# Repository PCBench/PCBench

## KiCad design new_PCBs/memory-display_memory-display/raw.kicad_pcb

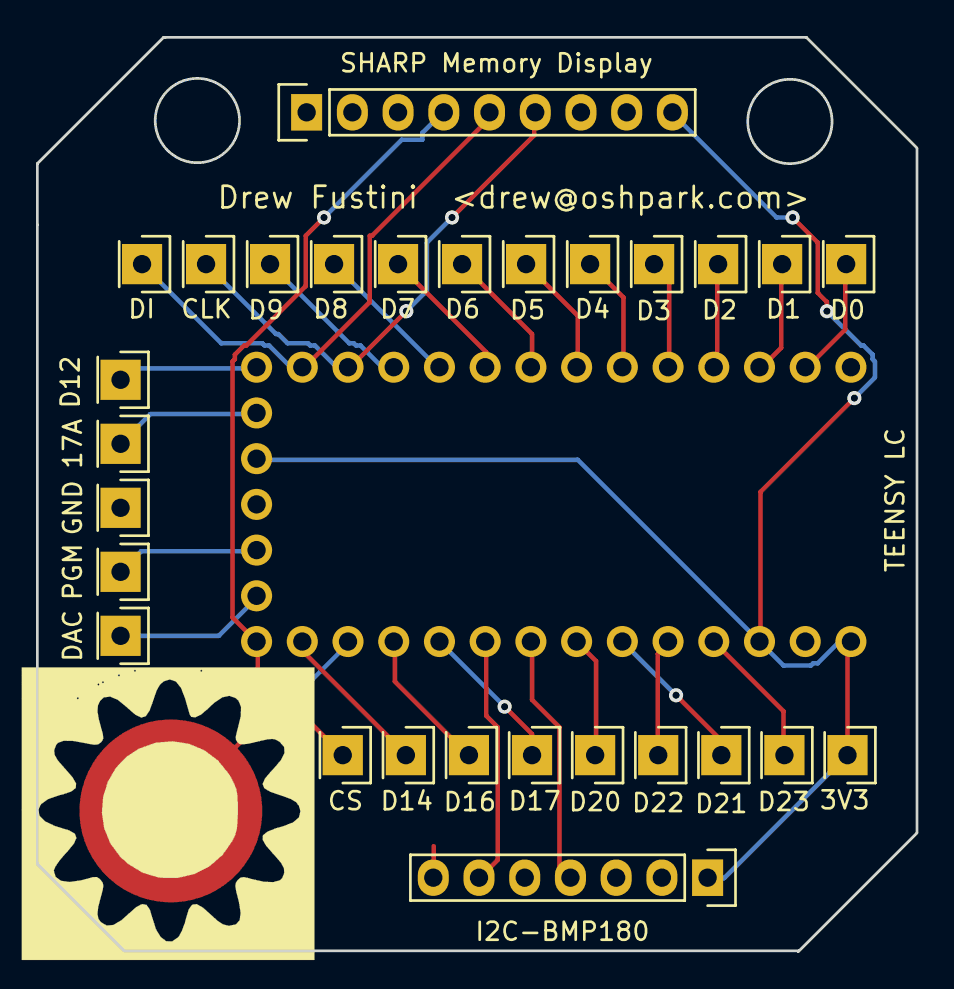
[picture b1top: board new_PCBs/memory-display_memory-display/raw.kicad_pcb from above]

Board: 2 copper layers, 48.9 x 50.8 mm, 30 parts (0 on the bottom side), 29 nets.

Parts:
3V3: 3v3; CONN-HEADER-STRAIGHT-P2.54MM-1x01
17A: 17A; CONN-HEADER-STRAIGHT-P2.54MM-1x01
CAP15: CAP15; CAPSENSE-CIRCLE-D10MM
CLK: CLK; CONN-HEADER-STRAIGHT-P2.54MM-1x01
CS: CS; CONN-HEADER-STRAIGHT-P2.54MM-1x01
D0: D0; CONN-HEADER-STRAIGHT-P2.54MM-1x01
D1: D1; CONN-HEADER-STRAIGHT-P2.54MM-1x01
D2: D2; CONN-HEADER-STRAIGHT-P2.54MM-1x01
D3: D3; CONN-HEADER-STRAIGHT-P2.54MM-1x01
D4: D4; CONN-HEADER-STRAIGHT-P2.54MM-1x01
D5: D5; CONN-HEADER-STRAIGHT-P2.54MM-1x01
D6: D6; CONN-HEADER-STRAIGHT-P2.54MM-1x01
D7: D7; CONN-HEADER-STRAIGHT-P2.54MM-1x01
D8: D8; CONN-HEADER-STRAIGHT-P2.54MM-1x01
D9: D9; CONN-HEADER-STRAIGHT-P2.54MM-1x01
D12: D12; CONN-HEADER-STRAIGHT-P2.54MM-1x01
D14: D14; CONN-HEADER-STRAIGHT-P2.54MM-1x01
D16: D16; CONN-HEADER-STRAIGHT-P2.54MM-1x01
D17: D17; CONN-HEADER-STRAIGHT-P2.54MM-1x01
D20: D20; CONN-HEADER-STRAIGHT-P2.54MM-1x01
D21: D21; CONN-HEADER-STRAIGHT-P2.54MM-1x01
D22: D22; CONN-HEADER-STRAIGHT-P2.54MM-1x01
D23: D23; CONN-HEADER-STRAIGHT-P2.54MM-1x01
DAC: DAC; CONN-HEADER-STRAIGHT-P2.54MM-1x01
DI: DI; CONN-HEADER-STRAIGHT-P2.54MM-1x01
GND: PGM; CONN-HEADER-STRAIGHT-P2.54MM-1x01
I2C-BMP180: I2C-BMP180; Pin_Header_Straight_1x07
J1: TEENSY-LC
PGM: PGM; CONN-HEADER-STRAIGHT-P2.54MM-1x01
SHARP Memory Display: SHARP-MEM-DISP; Pin_Header_Straight_1x09

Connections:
+3V3: 3V3.1, I2C-BMP180.1, J1.3V1, J1.3V2, J1.VIN, SHARP Memory Display.9
/CLK: CLK.1, J1.10, SHARP Memory Display.6
/CS: CS.1, I2C-BMP180.7, J1.13, SHARP Memory Display.4
/D0: D0.1, J1.0
/D1: D1.1, J1.1
/D2: D2.1, J1.2
/D3: D3.1, J1.3
/D4: D4.1, J1.4
/D5: D5.1, J1.5
/D6: D6.1, J1.6
/D7: D7.1, J1.7
/D8: D8.1, J1.8
/D9: D9.1, J1.9
/D11: DI.1, J1.11, SHARP Memory Display.5
/D12: D12.1, J1.12
/D14: D14.1, J1.14
/D15: CAP15.1, J1.15
/D16: D16.1, J1.16
/D17: D17.1, J1.17
/D17(VIN): 17A.1, J1.17A
/D18: I2C-BMP180.6, J1.18
/D19: I2C-BMP180.4, J1.19
/D20: D20.1, J1.20
/D21: D21.1, J1.21
/D22: D22.1, J1.22
/D23: D23.1, J1.23
/DAC: DAC.1, J1.DAC
/PROG: J1.PGM, PGM.1
GND: GND.1, I2C-BMP180.3, J1.G1, J1.G2, J1.G3, SHARP Memory Display.7

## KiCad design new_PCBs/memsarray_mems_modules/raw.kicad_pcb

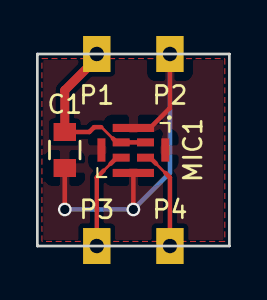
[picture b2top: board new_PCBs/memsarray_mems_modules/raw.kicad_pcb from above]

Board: 2 copper layers, 10.7 x 10.7 mm, 6 parts (0 on the bottom side), 4 nets.

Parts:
C1: 1uF; C_0805
MIC1: MEMS_MIC; Mic-MEMS_Top_8_pins
P1, P2, P3, P4: CASTELLATED_PAD; Castellated_Pad

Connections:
/CLK: MIC1.3, P3.1
/OUT: MIC1.4, P4.1
DGND: C1.2, MIC1.5, P2.1
DVDD: C1.1, MIC1.1, MIC1.2, P1.1

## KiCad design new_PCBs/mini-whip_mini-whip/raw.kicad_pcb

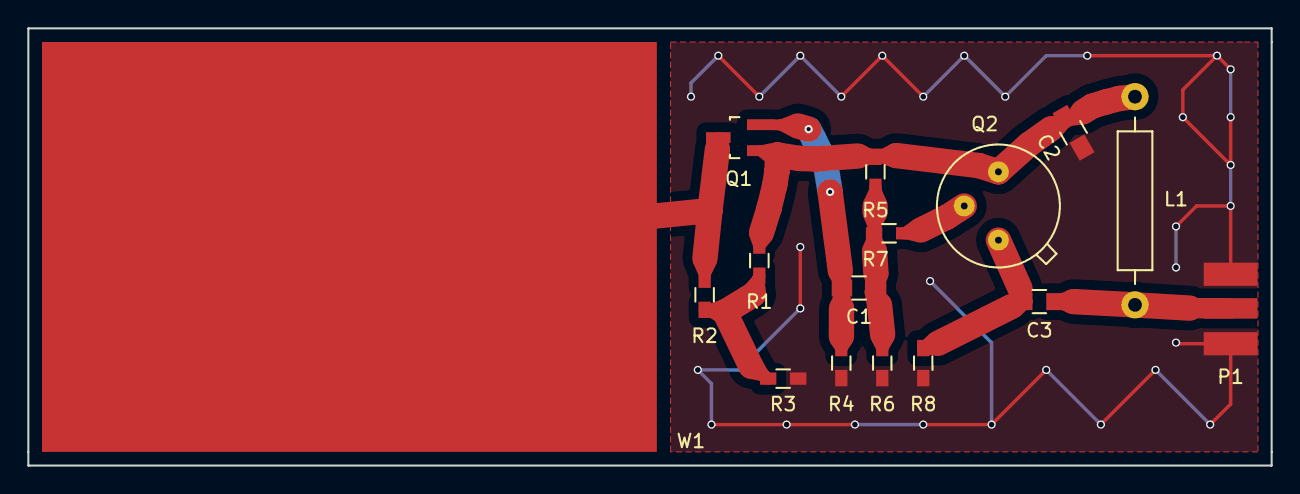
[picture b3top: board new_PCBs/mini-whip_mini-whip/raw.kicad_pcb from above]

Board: 2 copper layers, 91.0 x 32.0 mm, 17 parts (1 on the bottom side), 9 nets.

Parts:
C1, C2, C3: 560n; C_0805_HandSoldering
L1: 470 uH; Choke_Horizontal_RM15mm
P1, P1#2: SMA-J
Q1: MMBFJ310; SOT-23_Handsoldering
Q2: 2N5109; M246
R1, R2, R3: 1M; R_0603_HandSoldering
R4: 680; R_0603_HandSoldering
R5: 2k2; R_0603_HandSoldering
R6: 10k; R_0603_HandSoldering
R7: 47; R_0603_HandSoldering
R8: 220; R_0603_HandSoldering
W1: MINIWHIP

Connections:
Earth: C2.1, P1.2, P1#2.2, R3.2, R4.2, R6.2, R8.2
unnamed: C1.1, R5.2, R6.1, R7.2
unnamed: C1.2, Q1.2, R4.1
unnamed: C2.2, L1.1, Q1.1, Q2.3, R1.1, R5.1
unnamed: C3.1, L1.2, P1.1, P1#2.1
unnamed: C3.2, Q2.1, R8.1
unnamed: Q1.3, R2.1, W1.1
unnamed: Q2.2, R7.1
unnamed: R1.2, R2.2, R3.1

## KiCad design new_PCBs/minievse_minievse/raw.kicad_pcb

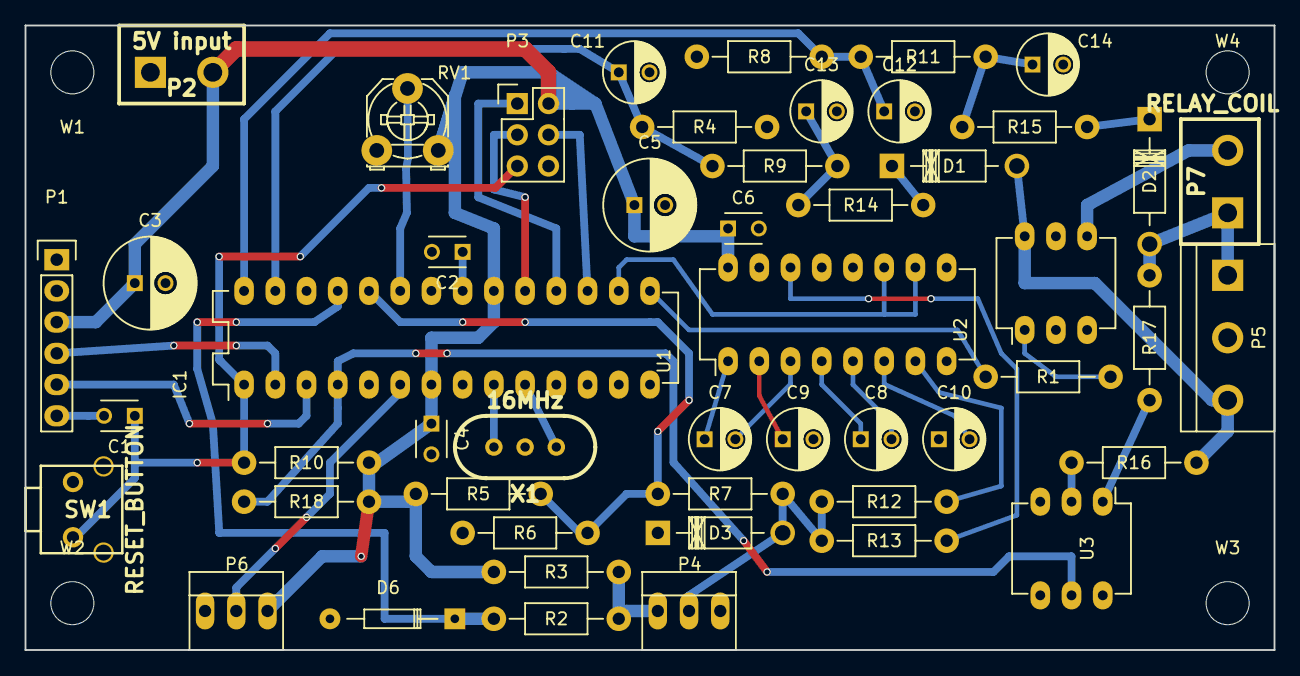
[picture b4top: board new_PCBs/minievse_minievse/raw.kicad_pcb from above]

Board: 2 copper layers, 101.6 x 50.8 mm, 54 parts (0 on the bottom side), 41 nets.

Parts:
C1, C2, C4, C6: 104; C_Disc_D3_P2.5
C3, C5: 100uF; C_Radial_D7.5_L11.2_P2.5
C7, C8, C9, C10: 1uF; C_Radial_D5_L6_P2.5
C11, C12, C13, C14: 10uF; C_Radial_D5_L6_P2.5
D1, D2: 1N4007; Diode_DO-41_SOD81_Horizontal_RM10_refdes_in_box
D3: P6KE16CA; Diode_DO-41_SOD81_Horizontal_RM10_refdes_in_box
D6: 1N4148; Diode_DO-35_SOD27_Horizontal_RM10
IC1: ATMEGA328P-P; DIP-28_W7.62mm_LongPads
P1: SERIAL; Pin_Header_Straight_1x06
P2: 5V input; CCFLHV
P3: ICSP; Pin_Header_Straight_2x03
P4: Pilot; PINHEAD1-3
P5: AC_GND_AC; bornier3
P6: LED_STRIP; PINHEAD1-3
P7: RELAY_COIL; CCFLHV
R1: 220; Resistor_Horizontal_RM10mm_refdes_in_box
R2, R10, R18: 10K; Resistor_Horizontal_RM10mm_refdes_in_box
R3: 1K; Resistor_Horizontal_RM10mm_refdes_in_box
R4, R8, R9, R11: 2550; Resistor_Horizontal_RM10mm_refdes_in_box
R5: 56K; Resistor_Horizontal_RM10mm_refdes_in_box
R6: 100K; Resistor_Horizontal_RM10mm_refdes_in_box
R7: 200K; Resistor_Horizontal_RM10mm_refdes_in_box
R12, R13: 1200; Resistor_Horizontal_RM10mm_refdes_in_box
R14, R15: 50K; Resistor_Horizontal_RM10mm_refdes_in_box
R16, R17: 15K; Resistor_Horizontal_RM10mm_refdes_in_box
RV1: POT; Potentiometer_Triwood_RM-065
SW1: RESET_BUTTON; SW-1825027-5
U1: MAX232; DIP-16_W7.62mm_LongPads
U2: MOC3021M; DIP-6_W7.62mm_LongPads
U3: H11AA; DIP-6_W7.62mm_LongPads
W1, W2, W3, W4: MountingHole_3.5mm
X1: 16MHz; HC-49V-OR-RESONATOR

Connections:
+5VD: C3.1, C4.1, C5.1, C6.1, IC1.7, IC1.20, P1.3, P2.2, P3.2, P6.3, R3.2, R5.1, R10.1, R18.1, RV1.3, U1.16
/AC_SENSE_1: C11.1, IC1.27, R4.1, R9.2
/AC_SENSE_2: C12.1, IC1.28, R8.1, R11.2
/AC_ZEROX: IC1.4, R18.2, U3.5
/AMP_KNOB: IC1.23, RV1.2
/LED_DATA: IC1.6, P6.2
/PILOT: D3.2, P4.2, R7.1, R12.1, R13.1
/PILOTREAD: IC1.24, R5.2, R6.1, R7.2
/PP: P4.1, R2.2, R3.1
/PP_READ: D6.1, IC1.25, R2.1
/PWM: IC1.16, U1.10, U1.11
/RELAY_TRIAC: IC1.15, R1.2
/RX: IC1.2, P1.4
/TX: IC1.3, P1.5
/miso: IC1.18, P3.1
/mosi: IC1.17, P3.4
/reset: C1.1, IC1.1, P3.5, R10.2, SW1.1
/sck: IC1.19, P3.3
GND: C2.2, C3.2, C4.2, C5.2, C6.2, C9.2, C10.1, C11.2, C12.2, C13.2, C14.2, D3.1, D6.2, IC1.8, IC1.22, P1.2, P2.1, P3.6, P4.3, P5.2, P6.1, R4.2, R6.2, R8.2, RV1.1, SW1.2, U1.15, U2.2, U3.4, X1.3
unnamed: C1.2, P1.6
unnamed: C2.1, IC1.21
unnamed: C7.1, U1.1
unnamed: C7.2, U1.3
unnamed: C8.1, U1.4
unnamed: C8.2, U1.5
unnamed: C9.1, U1.2
unnamed: C10.2, U1.6
unnamed: C13.1, R9.1, R14.1
unnamed: C14.1, R11.1, R15.1
unnamed: D2.2, P5.1, P7.1, R17.2
unnamed: D1.1, R14.2
unnamed: D1.2, P5.3, R16.2, U2.6
unnamed: D2.1, R15.2
unnamed: IC1.9, X1.2
unnamed: IC1.10, X1.1
unnamed: P7.2, U2.4
unnamed: R1.1, U2.1
unnamed: R12.2, U1.7
unnamed: R13.2, U1.14
unnamed: R16.1, U3.2
unnamed: R17.1, U3.1

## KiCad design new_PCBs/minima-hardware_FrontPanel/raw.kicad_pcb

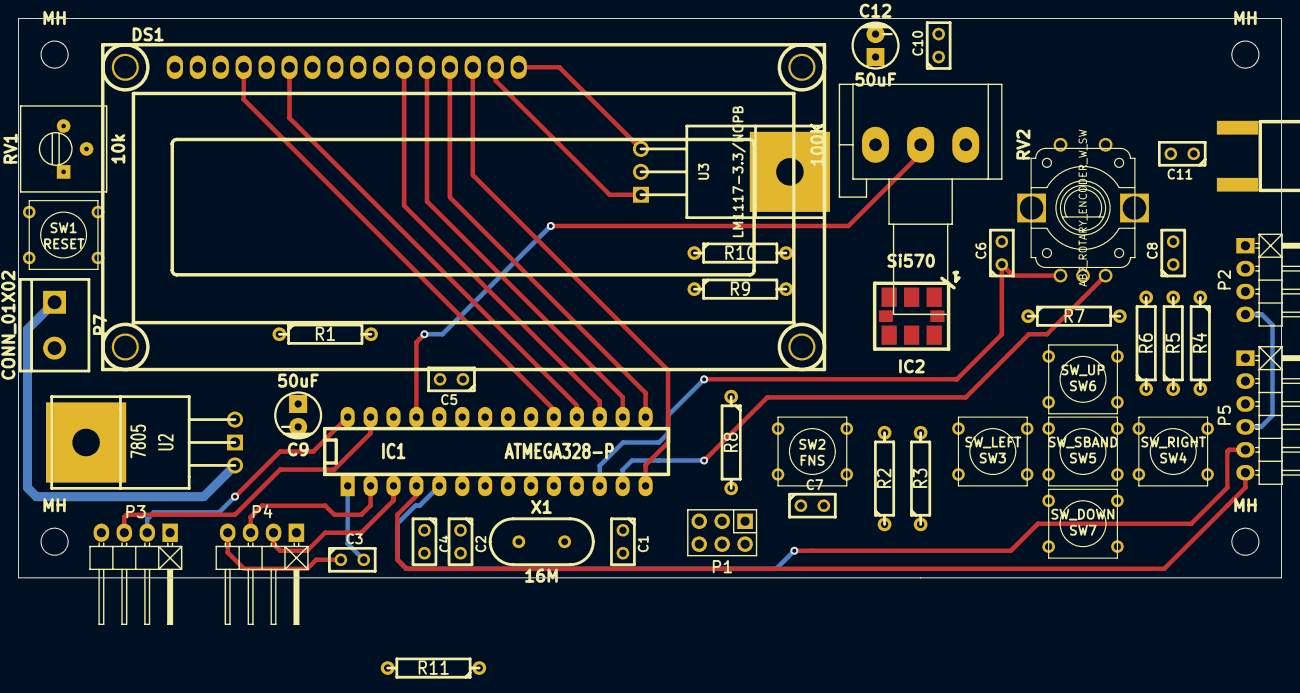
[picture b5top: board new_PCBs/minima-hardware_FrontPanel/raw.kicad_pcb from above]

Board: 2 copper layers, 140.0 x 62.0 mm, 50 parts (0 on the bottom side), 39 nets.

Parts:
C1, C2: 22pF; C1
C3: 0.1; C1
C4, C5: C; C1
C6, C7, C8: 1nF; C1
C9, C12: 50uF; Capacitor5x6RM2.5
C10, C11: .1uF; C1
DS1: LCD16X2; WC1602A
IC1: ATMEGA328-P; DIP-28__300_ELL
IC2: Si570; SI570_SI571_Standard
J1: sma; SMA_EDGE
MH: MountingHole_3mm_RevA_Date21Jun2010; MountingHole_3mm
MH#2, MH#3, MH#4: MountingHole_3mm_RevA_Date21Jun2010; MountingHole_3mm
P1: ICSP; Pin_Header_Straight_2x03
P2, P3, P4: CONN_01X04; Pin_Header_Angled_1x04
P5: CONN_01X06; Pin_Header_Angled_1x06
P7: CONN_01X02; bornier2
R1: 100K; R4
R2, R3, R4, R5, R6, R7: 4.7k; R4
R8: 47k; R4
R9, R10: 4.7K; R4
R11: 10K; R4
ROT_ENC1: AB2_ROTARY_ENCODER_W_SW; AB2_ROTARY_ENCODER_W_SWITCH
RV1: 10k; Potentiometer_Trimmer-Suntan-TSR-3386P
RV2: 100K; Potentiometer_Alps-RK16-single_largePads
SW1: RESET; SW_PUSH_SMALL
SW2: FNS; SW_PUSH_SMALL
SW3: SW_LEFT; SW_PUSH_SMALL
SW4: SW_RIGHT; SW_PUSH_SMALL
SW5: SW_SBAND; SW_PUSH_SMALL
SW6: SW_UP; SW_PUSH_SMALL
SW7: SW_DOWN; SW_PUSH_SMALL
U2: 7805; LM78XX
U3: LM1117-3.3/NOPB; TO220
X1: 16M; HC-49V

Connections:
+3.3V: C10.1, C12.1, IC2.6, P3.4, R9.1, R10.1, U3.3
+12V: P7.1, U2.VI
/D4: DS1.11, IC1.17, P1.4
/D5: DS1.12, IC1.16
/D6: DS1.13, IC1.15
/D7: DS1.14, IC1.14
/E: DS1.6, IC1.18, P1.1
/RS: DS1.4, IC1.19, P1.3
/TUNE: IC1.25, RV2.2
CWTONE: IC1.5, P5.5
GND: C1.2, C2.2, C4.2, C5.2, C6.2, C7.2, C8.2, C9.2, C10.2, C12.2, DS1.1, DS1.5, DS1.16, IC1.8, IC1.22, IC2.3, IC2.5, J1.2, P1.6, P2.1, P3.1, P4.1, P5.1, P7.2, ROT_ENC1.2, ROT_ENC1.4, RV1.1, RV2.1, SW1.2, SW2.2, SW3.2, SW4.2, SW5.2, SW6.2, SW7.2, U2.GND, U3.2
KEY: IC1.24, P5.2
unnamed: C1.1, IC1.10, X1.2
unnamed: C2.1, IC1.9, X1.1
unnamed: C3.2, IC1.1, P1.5, R11.2, SW1.1
unnamed: C5.1, IC1.20, R1.2
unnamed: C6.1, IC1.12, ROT_ENC1.1
unnamed: C7.1, IC1.26, R2.2, R8.1, SW2.1
unnamed: C8.1, IC1.13, ROT_ENC1.3
unnamed: C11.1, J1.1
unnamed: C11.2, IC2.4
unnamed: DS1.3, RV1.2
unnamed: IC1.21, R8.2
unnamed: R2.1, R3.2, SW3.1
unnamed: R3.1, R4.2, SW4.1
unnamed: R4.1, R5.2, SW5.1
unnamed: R5.1, R6.2, SW6.1
unnamed: R6.1, R7.2, SW7.1
unnamed: R7.1, ROT_ENC1.6
PTT: IC1.23, P5.3
RF386: IC1.11, P2.3
RTS: C3.1, P4.4
RX: IC1.3, P4.2
SCL: IC1.28, IC2.8, P3.2, R10.2
SDA: IC1.27, IC2.7, P3.3, R9.2
TX: IC1.2, P4.3
TX/RX: IC1.6, P2.4, P5.4
USB/LSB: IC1.4, P5.6
VCC: C4.1, C9.1, DS1.2, DS1.15, IC1.7, P1.2, R1.1, R11.1, RV1.3, RV2.3, U2.VO, U3.1

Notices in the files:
new_PCBs/memory-display_memory-display/raw.kicad_pcb:
Released under the CERN Open Hardware License v1.2
